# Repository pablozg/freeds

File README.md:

<h1 align="center">
    FreeDS
    <br>
    
</h1>

**⚠️ ATTENTION / ADVERTENCIA** The project has evolved through different licensing stages. Please check the version you are using:

* **v1.0.7 rev2:** Open Source (GPL-3.0). Source code available in this repo.
* **Betas (up to v1.0.21):** Distributed under CC BY-ND 4.0.
* **v2.0.0 and above:** Proprietary EULA. Requires **Per-Device Activation**.

You can get more info in the Telegram Channel: [http://t.me/freeds_es](http://t.me/freeds_es) or check the community manual: [Community Manual](https://docs.google.com/document/d/1-XLCqHEbpqEPi4geI4CbANmGxodExC__zDvND89xjIU)

**FreeDS** is a universal surplus manager, totally independent of the energy source (photovoltaic and/or wind), created by **Pablo Zerón**, tested by Aeizoon, and PCB Design by amcalo.

---

## 🔑 License & Activation (v2.0.0+)

Starting from **version 2.0.0**, FreeDS uses a **Proprietary EULA**. 

- **Ownership:** The software is the exclusive property of **Pablo Zerón**.
- **Cloud Services:** Powered and managed by **Ibepower Technologies S.L.**
- **Activation:** A unique **Activation Key** is required for each device (linked to Hardware ID).

### How to get a Key?
Send an email to **derivadorfreeds@gmail.com** with:
1. Your **Device ID** (visible on the screen/web interface).
2. **DIY/Contributors:** Proof of contribution or self-assembly (image of the device) to request a **free key**.
3. **Commercial Use:** Request a quote if you are selling hardware with FreeDS firmware.

---

## 📜 License History

| Version Range | License Type | Description |
| :--- | :--- | :--- |
| **<= v1.0.7 rev2** | [GPL-3.0](https://opensource.org/licenses/GPL-3.0) | Open Source. Original legacy code. |
| **v1.0.8 - v1.0.21** | [CC BY-ND 4.0](https://creativecommons.org/licenses/by-nd/4.0/) | Creative Commons. No derivatives allowed. |
| **>= v2.0.0** | **Proprietary EULA** | Proprietary. Requires activation key per hardware. |

*Full legal terms can be found in the [EULA.md](./EULA.md) file.*

---

## ☕ Donate
If you find this project useful, consider supporting its development:

---

## Dependencies (for legacy v1.0.7 compilation)
- **TickerScheduler**: [Toshik/TickerScheduler](https://github.com/Toshik/TickerScheduler)
- **Async MQTT client**: [marvinroger/async-mqtt-client](https://github.com/marvinroger/async-mqtt-client)
- **ArduinoJson**: [bblanchon/ArduinoJson](https://github.com/bblanchon/ArduinoJson)
- **AsyncTCP**: [me-no-dev/AsyncTCP](https://github.com/me-no-dev/AsyncTCP)
- **ESPAsyncWebServer**: [me-no-dev/ESPAsyncWebServer](https://github.com/me-no-dev/ESPAsyncWebServer)
- **ThingPulse OLED SSD1306**: [ThingPulse/esp8266-oled-ssd1306](https://github.com/ThingPulse/esp8266-oled-ssd1306)
- **esp32ModbusTCP**: [bertmelis/esp32ModbusTCP](https://github.com/bertmelis/esp32ModbusTCP)

## Compile (Legacy v1.0.7)
1. **Download:** Clone this repo or download the [PID.zip](https://github.com/pablozg/freeds/archive/refs/heads/PID.zip).
2. **Library Setup:** Extract `lib.zip` into the `/lib` folder.
3. **IDE:** Open with **VSCode** and **PlatformIO**.
4. **Build:** Use PlatformIO to compile and upload to your ESP32.

---
Copyright (c) 2026 Pablo Zerón. Cloud services provided by Ibepower Technologies S.L.

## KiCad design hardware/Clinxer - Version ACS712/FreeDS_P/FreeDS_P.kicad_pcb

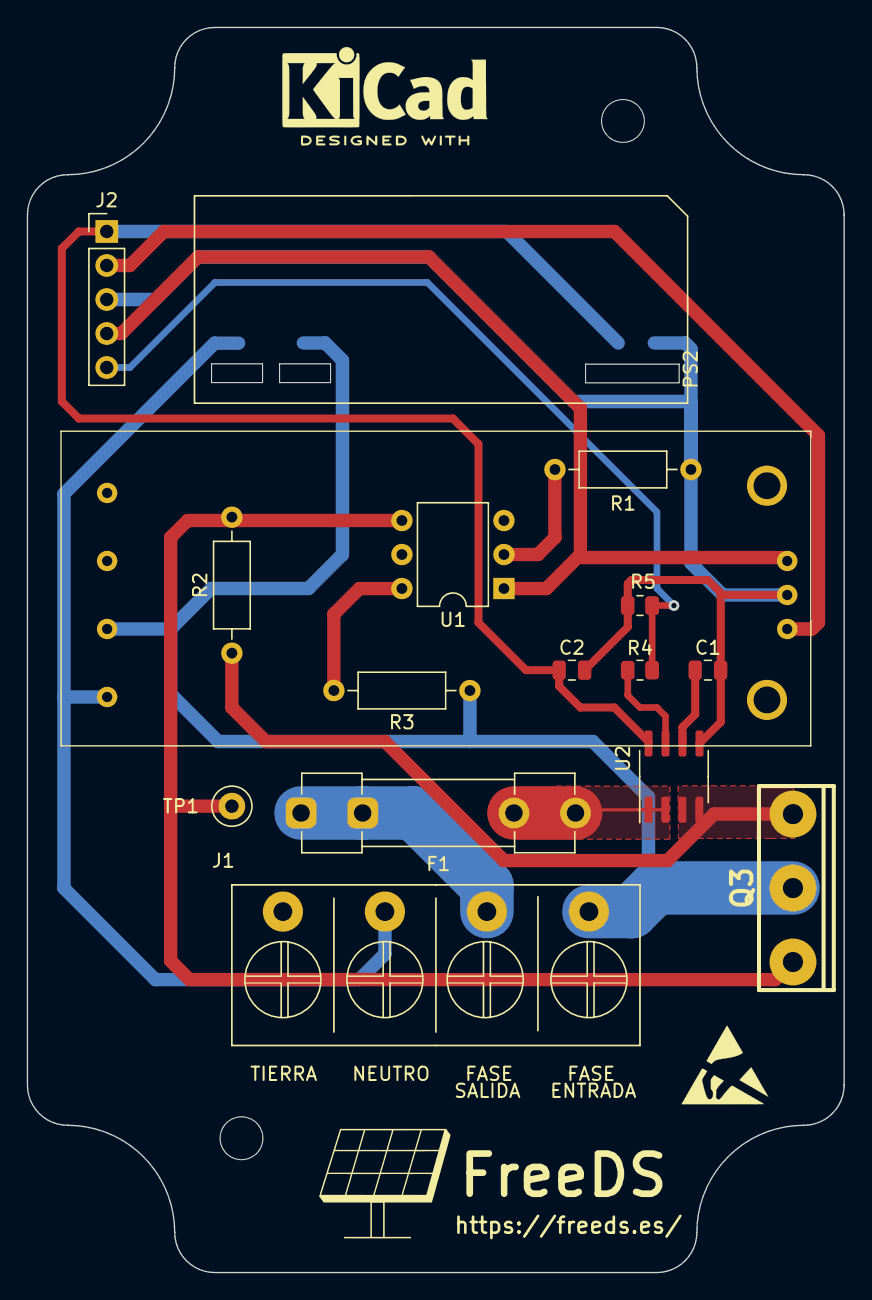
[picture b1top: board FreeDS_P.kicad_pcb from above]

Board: 2 copper layers, 61.0 x 93.0 mm, 19 parts (0 on the bottom side), 15 nets.

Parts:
C1: 1nF; C_0805_2012Metric
C2: 100nF; C_0805_2012Metric
F1: Fuse; Fuseholder_Clip-5x20mm_Littelfuse_100_Inline_P20.50x4.60mm_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
FreeDS: LOGO; FreeDS
H1, H2: MountingHole; MountingHole_3.2mm_M3
J1: Screw_Terminal_01x04; KF7.62_4P
J2: Conn_01x05; PinHeader_1x05_P2.54mm_Vertical
PS2: HLK-5M03; 5V10W
Q3: BTA26-600BW; TOP3_Vertical
R1: 180R; R_Axial_DIN0207_L6.3mm_D2.5mm_P10.16mm_Horizontal
R2: 330R; R_Axial_DIN0207_L6.3mm_D2.5mm_P10.16mm_Horizontal
R3: 360R; R_Axial_DIN0207_L6.3mm_D2.5mm_P10.16mm_Horizontal
R4: 1K; R_0805_2012Metric
R5: 2K; R_0805_2012Metric
TP1: TestPoint_Probe; TestPoint_Loop_D2.50mm_Drill1.0mm
U1: MOC3041M; DIP-6_W7.62mm
U2: ACS712xLCTR-30A; SOIC-8_3.9x4.9mm_P1.27mm
U5: YYAC-3S PWM TRIAC

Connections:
/3V3: J2.2, U5.1 (3.3/5V)
/+5V: C2.1, J2.1, PS2.4 (+Vout), U2.8 (VCC)
/A2_FUSE: Q3.1 (A1), R2.1, U2.3 (IP-), U2.4 (IP-)
/EN: J2.5, R4.2, R5.1
/GND: C1.2, C2.2, J2.3, PS2.3 (-Vout), R1.2, R5.2, U2.5 (GND), U5.2 (GND)
/Lin: J1.1, PS2.1 (AC/L), Q3.2 (A2), R3.1, U5.6 (L-IN_230V)
/Lout: F1.1, J1.2
/N: J1.3, PS2.2 (AC/N), U5.7 (N-IN_230V)
/PWM: J2.4, U1.1, U5.3 (PWM)
unnamed: F1.2, U2.1 (IP+), U2.2 (IP+)
unnamed: Q3.3 (G), R2.2, TP1.1, U1.4
unnamed: R1.1, U1.2
unnamed: R3.2, U1.6
unnamed: C1.1, U2.6 (FILTER)
unnamed: R4.1, U2.7 (VIOUT)

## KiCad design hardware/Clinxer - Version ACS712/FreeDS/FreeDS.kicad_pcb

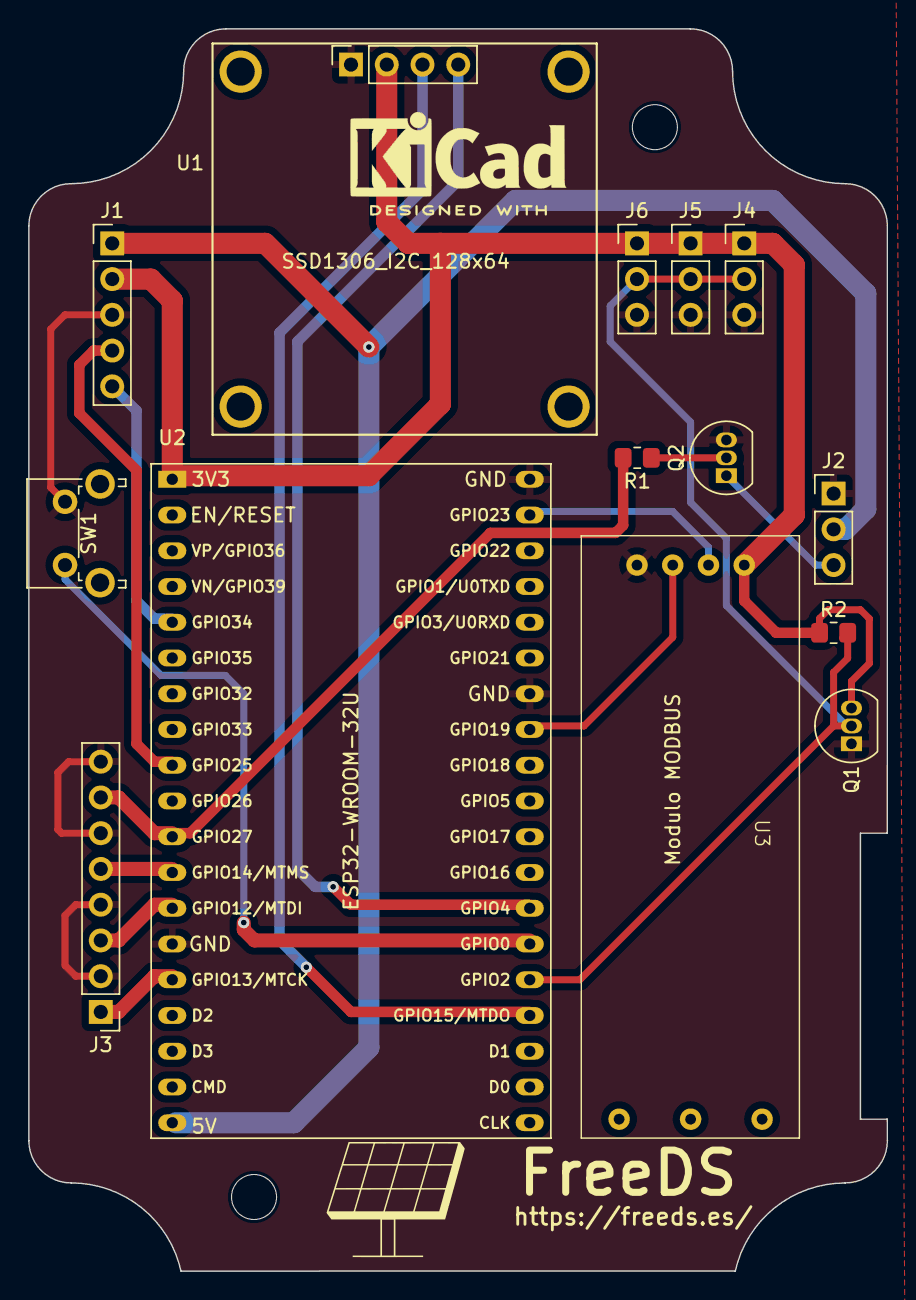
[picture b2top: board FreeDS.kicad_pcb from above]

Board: 2 copper layers, 61.0 x 88.3 mm, 17 parts (0 on the bottom side), 17 nets.

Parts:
FreeDS: LOGO; FreeDS
H1, H6: MountingHole; MountingHole_3.2mm_M3
J1: Conn_01x05; PinHeader_1x05_P2.54mm_Vertical
J2: VENTILADOR; PinHeader_1x03_P2.54mm_Vertical
J3: SALIDAS AUXILIARES; PinHeader_1x08_P2.54mm_Vertical
J4, J5, J6: Conn_01x03_Male; PinHeader_1x03_P2.54mm_Vertical
Q1: DS18B20; TO-92_Inline
Q2: BC337; TO-92_Inline
R1: 180R; R_0805_2012Metric_Pad1.20x1.40mm_HandSolder
R2: 4K7; R_0805_2012Metric_Pad1.20x1.40mm_HandSolder
SW1: PRG; SW_Tactile_SPST_Angled_PTS645Vx83-2LFS
U1: SSD1306_I2C_128x64; OLED_SSD1306_I2C_0.96
U2: ESP32-WROOM-32U; ESP32-DevKitC
U3: Modulo MODBUS; MW-519 MODBUS

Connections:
/3V3: J1.2, J4.1, J5.1, J6.1, Q1.3 (VDD), R2.1, U1.2 (VCC), U2.1 (3V3), U3.1 (VCC)
/+5V: J1.1, J2.2, U2.19 (5V)
/DQ_DS18B20: J4.2, J5.2, J6.2, Q1.2 (DQ), R2.2, U2.24 (ADC2_CH2/GPIO2)
/EN: J1.5, U2.5 (VDET_1/GPIO34/ADC1_CH6)
/GND: J1.3, J2.1, J3.2, J3.4, J3.6, J3.8, J4.3, J5.3, J6.3, Q1.1 (GND), Q2.3 (E), SW1.2 (B), U1.1 (GND), U2.14 (GND), U2.32 (GND), U2.38 (GND), U3.4 (GND)
/PWM: J1.4, U2.9 (DAC_1/ADC2_CH8/GPIO25)
/RELE_1: J3.1, U2.15 (MTCK/GPIO13/ADC2_CH4)
/RELE_2: J3.3, U2.13 (MTDI/GPIO12/ADC2_CH5)
/RELE_3: J3.5, U2.12 (MTMS/GPIO14/ADC2_CH6)
/RELE_4: J3.7, R1.2, U2.11 (ADC2_CH7/GPIO27)
/RX: U2.31 (GPIO19), U3.3 (RXD)
/SCL: U1.3 (SCL), U2.23 (MTDO/GPIO15/ADC2_CH3)
/SDA: U1.4 (SDA), U2.26 (ADC2_CH0/GPIO4)
/SW1: SW1.1 (A), U2.25 (GPIO0/BOOT/ADC2_CH1)
/TX: U2.37 (GPIO23), U3.2 (TXD)
unnamed: J2.3, Q2.1 (C)
unnamed: Q2.2 (B), R1.1

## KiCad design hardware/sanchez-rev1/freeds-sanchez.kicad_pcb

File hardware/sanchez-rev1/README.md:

La arquitectura "Sánchez rev1" se basa en las ideas de otras arquitecturas hardware para FreeDS, separando el diseño en dos PCBs que caben en las cajas estancas usadas por otras arquitecturas hardware.

La arquitectura Sánchez rev1 incluye:

- Conectores para RS485
- Conectores para sensores de temperatura
  - Espacio para un sensor montado en la parte inferior de la placa de control, pensado para que doblando las patillas pueda tocar el disipador del TRIAC
- Conectores para relés
  - Conector para ventilador controlado por relé 4
- Conectores para pinza amperimétrica
  - Conector de dos pines
  - Conector de jack de audio de 3.5mm

La novedad con respecto a otras arquitecturas es la circuitería y conectores para poder controlar un ventilador por PWM: la idea es que cuanto mayor sea el porcentaje de PWM, más trabajará el ventilador.

El diseño está hecho con KiCAD, y se incluyen los ficheros Gerber (ya compilados y por separado para cada una de las dos PCBs) para comodidad a la hora de pedir la fabricación de las placas.

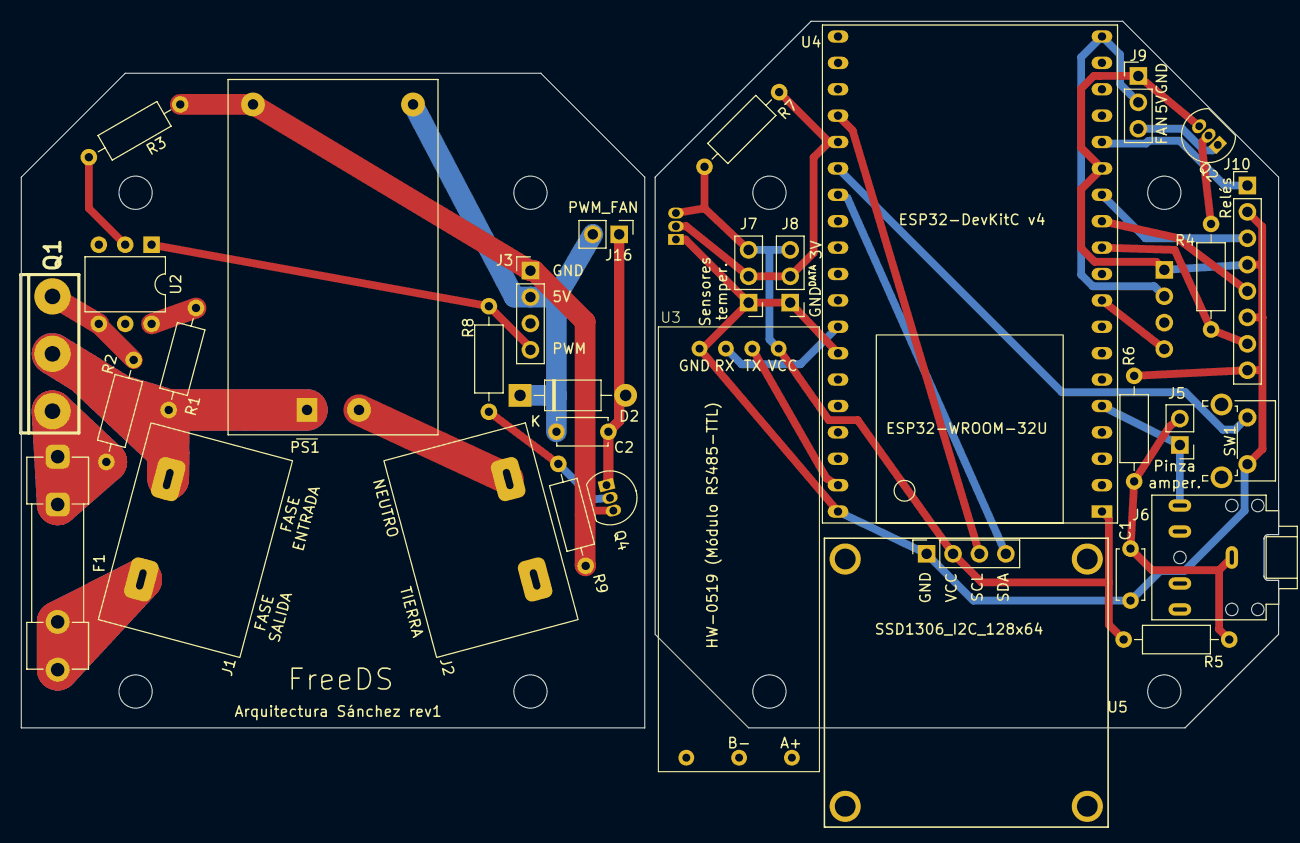
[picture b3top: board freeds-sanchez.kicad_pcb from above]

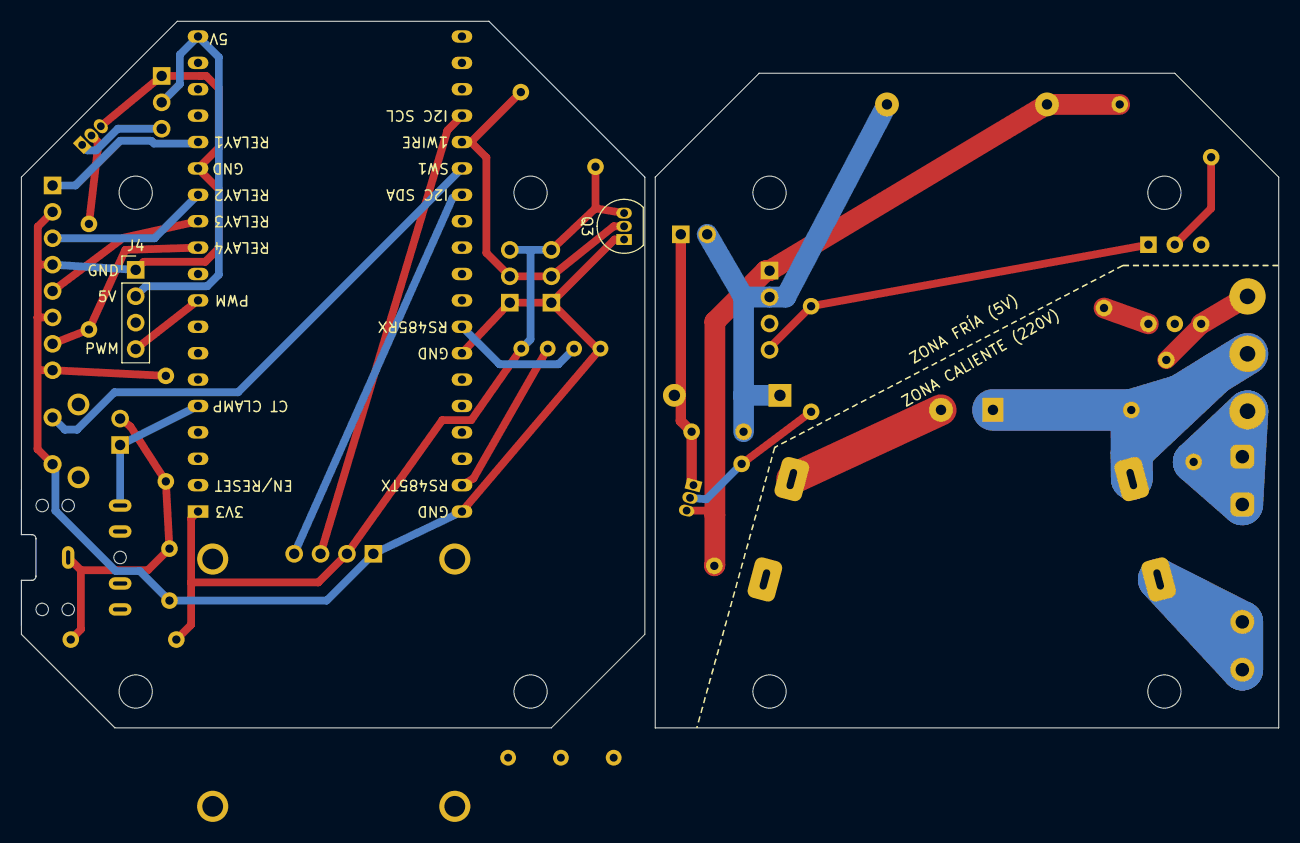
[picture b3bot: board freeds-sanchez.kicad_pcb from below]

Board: 2 copper layers, 121.0 x 68.0 mm, 42 parts (2 on the bottom side), 30 nets.

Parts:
C1, C2: 10µF; C_Disc_D4.7mm_W2.5mm_P5.00mm
D2: 1N4007; D_DO-41_SOD81_P10.16mm_Horizontal
F1: Fuse; Fuseholder_Clip-5x20mm_Littelfuse_100_Inline_P20.50x4.60mm_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
H2, H2#2, H3, H3#2, H4, H4#2, H5, H5#2: MountingHole; MountingHole_3.2mm_M3
J1, J2: Clema K1000; Clema 20x14mm K1000 2P
J3, J4: Inter-PCB; PinHeader_1x04_P2.54mm_Vertical
J5: Pinza Amper.; PinHeader_1x02_P2.54mm_Vertical
J6: CT Clamp; Jack_3.5mm_CUI_SJ1-3525N_Horizontal
J7: Temp sensor; PinHeader_1x03_P2.54mm_Vertical
J8: Temp Sensor; PinHeader_1x03_P2.54mm_Vertical
J9: R4_FAN; PinHeader_1x03_P2.54mm_Vertical
J10: RELÉS; PinHeader_1x08_P2.54mm_Vertical
J16: Conn_01x02_Male; PinHeader_1x02_P2.54mm_Vertical
PS1: HLK-PM01; Converter_ACDC_HiLink_HLK-PMxx
Q1: BTA26-600BW; TOP3_Vertical
Q2: BC337; TO-92_Inline
Q3: DS18B20; TO-92_Inline
Q4: BS170; TO-92_Inline
R1: 360Ω; R_Axial_DIN0207_L6.3mm_D2.5mm_P10.16mm_Horizontal
R2: 330Ω; R_Axial_DIN0207_L6.3mm_D2.5mm_P10.16mm_Horizontal
R3, R4: 180Ω; R_Axial_DIN0207_L6.3mm_D2.5mm_P10.16mm_Horizontal
R5, R6, R9: 10KΩ; R_Axial_DIN0207_L6.3mm_D2.5mm_P10.16mm_Horizontal
R7: 4.7KΩ; R_Axial_DIN0207_L6.3mm_D2.5mm_P10.16mm_Horizontal
R8: 3.3Ω; R_Axial_DIN0207_L6.3mm_D2.5mm_P10.16mm_Horizontal
SW1: PRG; SW_Tactile_SPST_Angled_PTS645Vx83-2LFS
U2: MOC3041M; DIP-6_W7.62mm
U3: HW-0519 (Módulo RS485-TTL); HW-519 TTL-RS485
U4: ESP32-WROOM-32U; ESP32-DevKitC
U5: SSD1306_I2C_128x64; OLED_SSD1306_I2C_0.96

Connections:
1WIRE: J7.2, J8.2, Q3.2 (DQ), R7.2, U4.24 (ADC2_CH2/GPIO2)
+3V3: J7.3, J8.3, Q3.3 (VDD), R5.1, R7.1, U3.1 (VCC), U4.1 (3V3), U5.2 (VCC)
+5V: J4.2, J9.2, U4.19 (5V)
/control/SW1: SW1.1 (A), U4.25 (GPIO0/BOOT/ADC2_CH1)
/potencia/+5V: C2.2, D2.1 (K), J3.2, J16.2, PS1.4 (+Vout)
/potencia/A1: F1.1, Q1.1 (A1), R2.1
/potencia/GND: J3.1, PS1.3 (-Vout), Q4.3 (S), R3.2, R9.1
/potencia/Gate: Q1.3 (G), R2.2, U2.4
/potencia/PWM POTENCIA: J3.4, R8.1, U2.1
CT CLAMP: J5.1, J6.T, U4.5 (VDET_1/GPIO34/ADC1_CH6)
GND: C1.2, J4.1, J7.1, J8.1, J9.1, J10.2, J10.4, J10.6, J10.8, Q2.3 (E), Q3.1 (GND), R6.2, SW1.2 (B), U3.4 (GND), U4.14 (GND), U4.32 (GND), U4.38 (GND), U5.1 (GND)
I2C SCL: U4.23 (MTDO/GPIO15/ADC2_CH3), U5.3 (SCL)
I2C SDA: U4.26 (ADC2_CH0/GPIO4), U5.4 (SDA)
LINE IN: J1.2, PS1.1 (AC/L), Q1.2 (A2), R1.1
LINE OUT: F1.2, J1.1
NEUT: J2.1, PS1.2 (AC/N)
unnamed: C2.1, D2.2 (A), J16.1, Q4.1 (D)
unnamed: C1.1, J5.2, J6.S, R5.2, R6.1
unnamed: J9.3, Q2.1 (C)
unnamed: Q2.2 (B), R4.1
unnamed: Q4.2 (G), R8.2, R9.2
unnamed: R1.2, U2.6
unnamed: R3.1, U2.2
PWM: J4.4, U4.9 (DAC_1/ADC2_CH8/GPIO25)
RELAY1: J10.1, U4.15 (MTCK/GPIO13/ADC2_CH4)
RELAY2: J10.3, U4.13 (MTDI/GPIO12/ADC2_CH5)
RELAY3: J10.5, U4.12 (MTMS/GPIO14/ADC2_CH6)
RELAY4: J10.7, R4.2, U4.11 (ADC2_CH7/GPIO27)
RS485RX: U3.3 (RXD), U4.31 (GPIO19)
RS485TX: U3.2 (TXD), U4.37 (GPIO23)

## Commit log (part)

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2020-02-28 Versión 1.0.0 Beta
2020-03-01 Librerias actualizadas, añadido contador de tiempo en funcionamiento a la página de información (oled) y ajustes estéticos página web.
2020-03-01 Actualización de librerías
2020-03-01 Eliminada función duplicada
2020-03-11 Actualizada la versión a 1.0.2
2020-03-11 Correción en la reserva de variables en Estructura Config
2020-03-11 Añadida comprobación que impedia la grabación de la IP en el caso del wibeee
2020-03-24 Update LICENSE
2020-03-26 Actualizado a versión 1.0.4
2020-03-26 cambiada codificación en Changelog a UTF8
2020-05-07 try fix travis
2020-05-25 Revisión 10
2020-05-25 Update Fauxmo Lib
2020-07-20 Update to last changes
2020-07-20 Revert Delete libs
2020-07-20 Add Libs
2020-10-26 Upload actual progress, rev 15.
2020-10-26 Added Portuguese translation (OLED Screen)
2020-10-27 Some changes on SMA inverters and fix some bad coding day.
2020-10-27 Fix Web issues
2020-11-01 Upload new release
    Versión 1.0.5 (Versión Final)
    - Modificada la gestión de temperatura para evitar falsos errores
    - Cambiados los tiempos mínimos de adquisición de datos (Modbus 250ms, Modbus TCP 1000ms (Fronius 250ms), Slave 250ms, Solax con ESP01 fijo a 250ms, HTTP API 1500ms)
    - Añadido contador básico de energia consumida y vertida según los datos de Red
    - Añadido comando "flipScreen" (desde la consola) para invertir la pantalla Oled
    - Añadido funcionamiento en instalación aislada (OFF-GRID)
2020-11-16 Versión 1.0.6
    - Solucionado error en el cálculo de potencia consumida/vertida
    - Añadida comprobación para evitar multiples intentos de puesta en hora con equipos sin conexión o problemas de conectividad.
    - Solucionado lectura de datos erroneos en el Solax X1 Generación 3 (ESP01), es necesario escribir en la consola el comando: "solaxVersion 3", para elegir
    el nuevo modo de procesado de datos, si se desea volver al anterior escribir: "solaxVersion 2", es imprescindible hacerlo con el ESP01 conectado y funcionando.
    - Añadido comando para elegir la zona horaria, es necesario elegir la configuración correcta del fichero TimeZones.txt y escribir el siguiente comando en la consol
2020-11-16 Fix Travis
2020-11-18 Sync commit
2020-11-18 Upload language files
2020-11-22 Fix change AUTO/MAN with temp sensor enabled.
2020-12-10 Push 1.0.7 Changes
2020-12-24 First PID implementation
2020-12-24 PID Library with some changes
2020-12-28 improvements
2020-12-28 invert sign fix
2020-12-28 update arduino json
2020-12-31 Fix low cost output
2021-01-03 Code cleanup
2021-01-05 bug fixes and soft transition between AUTO and MANUAL modes.
2021-01-12 Bug Fixes
2021-01-20 1.0.7 Fixes
2021-01-20 fixes
2021-02-20 Bump to 1.0.7 Final
2021-05-23 Some fixes and changes
2021-05-23 Upload Lib files in a zip
2021-06-29 Update README.md
    Restyled from README.md
2021-07-12 doc: Updated adn fixed galician language texstrings
2021-08-07 fix: fixed external libs for compilation
2021-08-09 feat: added support Goodwe EH
2021-10-16 Increase pwd chars to 63 and increase witdh
2021-12-03 Added Topics and Solaredge description
    Added Topics in MQTT (ICC and Tasmota) and Solaredge memmory Address descrition.
2022-09-08 Update lang-ca.js
    Corregidos varios errores gramaticales, de ortografía y de estilo y completada la traducción.
2022-09-08 Update lang-ca.json
    Corregidos varios errores gramaticales y de estilo.
2022-11-22 Make it compile again
2022-11-22 Fix bad commit
2023-01-13 PCB Scheme upload
2023-03-07 Eula added
2023-03-07 Update EULA
2023-05-27 Añadidos ficheros de PCB de @clinxer
2023-06-02 Correcciones en arquitectura clinxer
2023-06-12 Corrección arq. clinxer: pines de optoacoplador
2023-12-02 Añadidos ficheros de arquitectura hardware "Sánchez rev1"
2023-12-08 New version with ACS712
2024-09-17 Change licences
2025-12-30 Update EULA with legal terms and privacy policy
    Added legal terms, privacy policy, and conditions of use for FreeDS, including data protection information and user rights.
2026-03-18 Revise EULA for FreeDS with new terms and conditions
    Updated EULA with new ownership and activation terms.
2026-03-18 Rename EULA to EULA.md
2026-03-18 Revise README with updated licensing details
    Updated license information and project description in README.
2026-06-10 Upload OTA test firmware 2.0.5 WIFIKIT32
2026-06-10 Upload OTA test firmware 2.0.4 WIFIKIT32
2026-06-10 Add OTA firmware 2.0.4 WIFIKIT32 to manifest
2026-06-10 Clean OTA manifest and preserve 2.0.4/2.0.5
2026-06-10 Upload OTA test firmware 2.0.4 WROOM32-NOSCREEN
2026-06-10 Upload OTA test firmware 2.0.4 WROOM32-OLED
2026-06-10 Upload OTA test firmware 2.0.4 WROOM32-SSH1106
2026-06-10 Add OTA firmware 2.0.4 release environments to manifest
